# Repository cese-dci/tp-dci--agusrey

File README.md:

Poncho PLC para CIAA7 - Agustín Rey

## Esquemático y PCB

Este repositorio contiene el los diagramas esquematicos y diseño de PCB del poncho PLC para la nueva placa CIAA7

### Estado Actual
Esquemático Terminado - Ruteo terminado - BOM Terminado
###
NOTA: El solapamiento de los bornes en el PCB es a propósito, porque asi pueden usarse
bornes de distinto número de polos a gusto del usuario.

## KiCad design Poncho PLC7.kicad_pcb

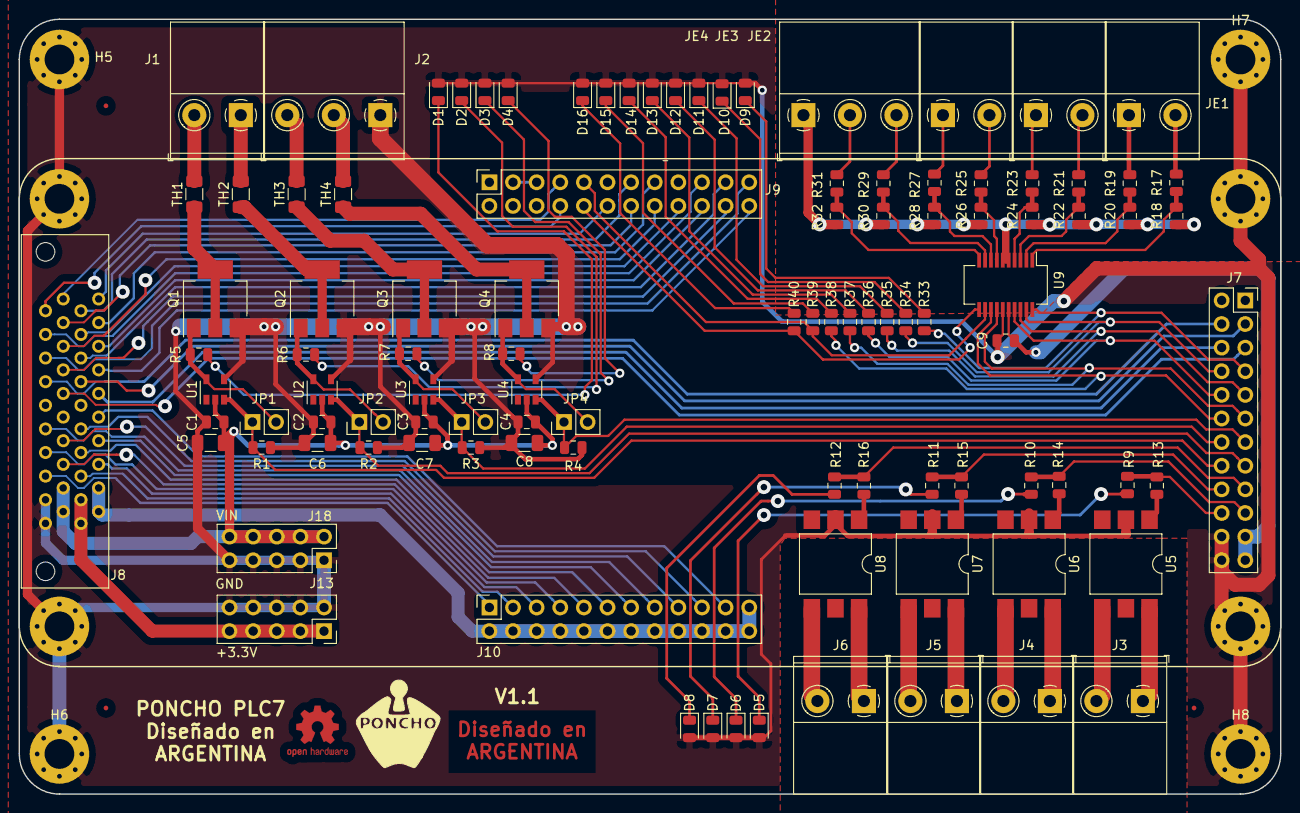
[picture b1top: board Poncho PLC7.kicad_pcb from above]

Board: 2 copper layers, 135.6 x 83.3 mm, 115 parts (0 on the bottom side), 108 nets.

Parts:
 : OSHW-Logo2_7.3x6mm_Copper
 #2: Logo_Poncho
C1, C2, C3, C4, C9: 100nF; C_0805_2012Metric
C5, C6, C7, C8: 1uF; C_1206_3216Metric
D1, D2, D3, D4, D5, D6, D7, D8, D9, D10, D11, D12, D13, D14, D15, D16: LED red; LED_0805_2012Metric
FID1, FID2, FID3: Fiducial; Fiducial_0.5mm_Mask1mm
H1, H2, H3, H4, H5, H6, H7, H8: MountingHole; MountingHole_3.2mm_M3_Pad_Via
J1: TB_1X2-PonchoPLC-rescue; TerminalBlock_WECO_120-M-311_1x02_P5.00mm_Plug-in_PCB
J2: TB_1X3-PonchoPLC-rescue; TerminalBlock_WECO_120-M-311_1x03_P5.00mm_Plug-in_PCB
J3, J4, J5, J6: TB_1X3-PonchoPLC-rescue; TerminalBlock_WECO_120-M-311_1x02_P5.00mm_Plug-in_PCB
J7, J9, J10: Conn_02x12_Odd_Even; PinSocket_2x12_P2.54mm_Vertical
J8: Conn_02x20_Counter_Clockwise; TX24-40R-LT-H1E
J13, J18: Conn_02x05_Odd_Even; PinSocket_2x05_P2.54mm_Vertical
JE1, JE2, JE3: TB_1X2-PonchoPLC-rescue; TerminalBlock_WECO_120-M-311_1x02_P5.00mm_Plug-in_PCB
JE4: TB_1X3-PonchoPLC-rescue; TerminalBlock_WECO_120-M-311_1x03_P5.00mm_Plug-in_PCB
JP1, JP2, JP3, JP4: Jumper; PinHeader_1x02_P2.54mm_Vertical
Q1, Q2, Q3, Q4: FQT13N06L; SOT-223
R1, R2, R3, R4: 100K; R_0805_2012Metric
R5, R6, R7, R8, R9, R10, R11, R12, R13, R14, R15, R16, R33, R34, R35, R36, R37, R38, R39, R40: 330; R_0805_2012Metric
R17, R19, R21, R23, R25, R27, R29, R31: 6.2K; R_0805_2012Metric
R18, R20, R22, R24, R26, R28, R30, R32: 2.7K; R_0805_2012Metric
TH1, TH2, TH3, TH4: PTS12066V100; R_1206_3216Metric
U1, U2, U3, U4: MCP1416; SOT-23-5
U5, U6, U7, U8: VO14642AABTR; SMDIP-6_W9.53mm
U9: SI8380P-IU; QSOP-20_3.9x8.7mm_P0.635mm

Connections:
+3.3VP: J8.21, J8.22, J13.1, J13.3, J13.5, J13.7, J13.9
+3V3: C9.2, J7.21, J7.23, U9.16
+5V: C1.2, C2.2, C3.2, C4.2, C5.2, C6.2, C7.2, C8.2, J8.11, J8.12, J18.2, J18.4, J18.6, J18.8, J18.10, U1.2, U2.2, U3.2, U4.2
/BaseCIAA7/ADC1_INP16: J8.13, J10.9
/BaseCIAA7/ADC3_INP1: J8.4, J10.7
/BaseCIAA7/ADC12_INN1_INP0: J8.33, J10.5
/BaseCIAA7/ADC12_INN5_INP9: J8.35, J10.21
/BaseCIAA7/ADC12_INP3: J8.14, J10.17
/BaseCIAA7/ADC12_INP5: J8.25, J10.19
/BaseCIAA7/ADC12_INP15: J8.24, J10.11
/BaseCIAA7/ADC12_INP18: J8.34, J10.13
/BaseCIAA7/ADC12_INP19: J8.5, J10.15
/BaseCIAA7/ADC123_INP10: J8.23, J10.3
/BaseCIAA7/IN0: J7.7, R33.2, U9.20
/BaseCIAA7/IN1: J7.8, R34.2, U9.19
/BaseCIAA7/IN2: J7.9, R35.2, U9.18
/BaseCIAA7/IN3: J7.10, R36.2, U9.17
/BaseCIAA7/IN4: J7.11, R37.2, U9.14
/BaseCIAA7/IN5: J7.12, R38.2, U9.13
/BaseCIAA7/IN6: J9.9, R39.2, U9.12
/BaseCIAA7/IN7: J9.10, R40.2, U9.11
/BaseCIAA7/OUT0: J7.16, JP1.1, R1.1, U1.3
/BaseCIAA7/OUT1: J7.15, JP2.1, R2.1, U2.3
/BaseCIAA7/OUT2: J7.14, JP3.1, R3.1, U3.3
/BaseCIAA7/OUT3: J7.13, JP4.1, R4.1, U4.3
/BaseCIAA7/OUT4: J7.20, R9.2, R13.2
/BaseCIAA7/OUT5: J7.19, R10.2, R14.2
/BaseCIAA7/OUT6: J7.18, R11.2, R15.2
/BaseCIAA7/OUT7: J7.17, R12.2, R16.2
/BaseCIAA7/PA8: J7.3, J8.27
/BaseCIAA7/PA15: J8.8, J9.23
/BaseCIAA7/PB3: J8.29, J9.18
/BaseCIAA7/PB4: J8.39, J9.15
/BaseCIAA7/PB5: J8.18, J9.16
/BaseCIAA7/PB6: J8.30, J9.13
/BaseCIAA7/PB7: J8.19, J9.14
/BaseCIAA7/PC6: J7.6, J8.36
/BaseCIAA7/PC7: J7.5, J8.16
/BaseCIAA7/PC9: J7.4, J8.7
/BaseCIAA7/PC10: J8.37, J9.24
/BaseCIAA7/PC13: J8.3, J10.1
/BaseCIAA7/PD3: J8.28, J9.21
/BaseCIAA7/PD4: J8.17, J9.22
/BaseCIAA7/PD5: J8.9, J9.19
/BaseCIAA7/PD6: J8.38, J9.20
/BaseCIAA7/PE2: J8.40, J9.12
/BaseCIAA7/PE5: J8.20, J9.7
/BaseCIAA7/PE6: J8.10, J9.8
/Entradas/A1: R17.1, R18.1, U9.1
/Entradas/A2: R19.1, R20.1, U9.2
/Entradas/A3: R21.1, R22.1, U9.3
/Entradas/A4: R23.1, R24.1, U9.4
/Entradas/A5: R25.1, R26.1, U9.7
/Entradas/A6: R27.1, R28.1, U9.8
/Entradas/A7: R29.1, R30.1, U9.9
/Entradas/A8: R31.1, R32.1, U9.10
GND: C1.1, C2.1, C3.1, C4.1, C5.1, C6.1, C7.1, C8.1, C9.1, D1.2, D2.2, D3.2, D4.2, D5.2, D6.2, D7.2, D8.2, D9.2, D10.2, D11.2, D12.2, D13.2, D14.2, D15.2, D16.2, H1.1, H2.1, H3.1, H4.1, H5.1, H6.1, H7.1, H8.1, J2.1, J7.22, J7.24, J8.1, J8.2, J13.2, J13.4, J13.6, J13.8, J13.10, J18.1, J18.3, J18.5, J18.7, J18.9, Q1.3, Q2.3, Q3.3, Q4.3, R1.2, R2.2, R3.2, R4.2, U1.4, U2.4, U3.4, U4.4, U5.2, U6.2, U7.2, U8.2, U9.15
GNDA: J8.31, J8.32, J10.2, J10.4, J10.6, J10.8, J10.10, J10.12, J10.14, J10.16, J10.18, J10.20, J10.22, J10.23, J10.24
GNDREF: JE4.1, R18.2, R20.2, R22.2, R24.2, R26.2, R28.2, R30.2, R32.2, U9.5, U9.6
unnamed: D1.1, R5.1
unnamed: D2.1, R6.1
unnamed: D3.1, R7.1
unnamed: D4.1, R8.1
unnamed: D5.1, R9.1
unnamed: D6.1, R10.1
unnamed: D7.1, R11.1
unnamed: D8.1, R12.1
unnamed: D9.1, R33.1
unnamed: D10.1, R34.1
unnamed: D11.1, R35.1
unnamed: D12.1, R36.1
unnamed: D13.1, R37.1
unnamed: D14.1, R38.1
unnamed: D15.1, R39.1
unnamed: D16.1, R40.1
unnamed: J1.1, TH2.2
unnamed: J1.2, TH1.2
unnamed: J2.2, TH4.2
unnamed: J2.3, TH3.2
unnamed: J3.1, U5.6
unnamed: J3.2, U5.4
unnamed: J4.1, U6.6
unnamed: J4.2, U6.4
unnamed: J5.1, U7.6
unnamed: J5.2, U7.4
unnamed: J6.1, U8.6
unnamed: J6.2, U8.4
unnamed: J9.3, J9.5
unnamed: JE1.1, R19.2
unnamed: JE1.2, R17.2
unnamed: JE2.1, R23.2
unnamed: JE2.2, R21.2
unnamed: JE3.1, R27.2
unnamed: JE3.2, R25.2
unnamed: JE4.2, R31.2
unnamed: JE4.3, R29.2
unnamed: JP1.2, Q1.1, R5.2, U1.5
unnamed: JP2.2, Q2.1, R6.2, U2.5
unnamed: JP3.2, Q3.1, R7.2, U3.5
unnamed: JP4.2, Q4.1, R8.2, U4.5
unnamed: Q1.2, Q1.4, TH1.1
unnamed: Q2.2, Q2.4, TH2.1
unnamed: Q3.2, Q3.4, TH3.1
unnamed: Q4.2, Q4.4, TH4.1
unnamed: R13.1, U5.1
unnamed: R14.1, U6.1
unnamed: R15.1, U7.1
unnamed: R16.1, U8.1

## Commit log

2019-10-01 mi primer commit
2019-10-10 version 2
2019-10-10 version 3
2019-10-18 Version 4
2019-10-23 Ruteo Parcial-Replanteo Esquematico pafa favorecer ruteo
2019-10-23 Ruteo Parcial-Replanteo Esquematico pafa favorecer ruteo 2
2019-10-23 Ruteo Parcial-Replanteo Esquematico pafa favorecer ruteo 3
2019-10-24 Ruteo Parcial-Replanteo Esquematico pafa favorecer ruteo v4
2019-10-25 Ruteo Casi terminado (faltan planos de masa)
2019-10-25 readme
2019-10-30 Esq y Ruteo 100% - falta Bom
2019-10-31 Esq + PCB + Bom terminados
2019-11-18 Agregado Leds Entradas
